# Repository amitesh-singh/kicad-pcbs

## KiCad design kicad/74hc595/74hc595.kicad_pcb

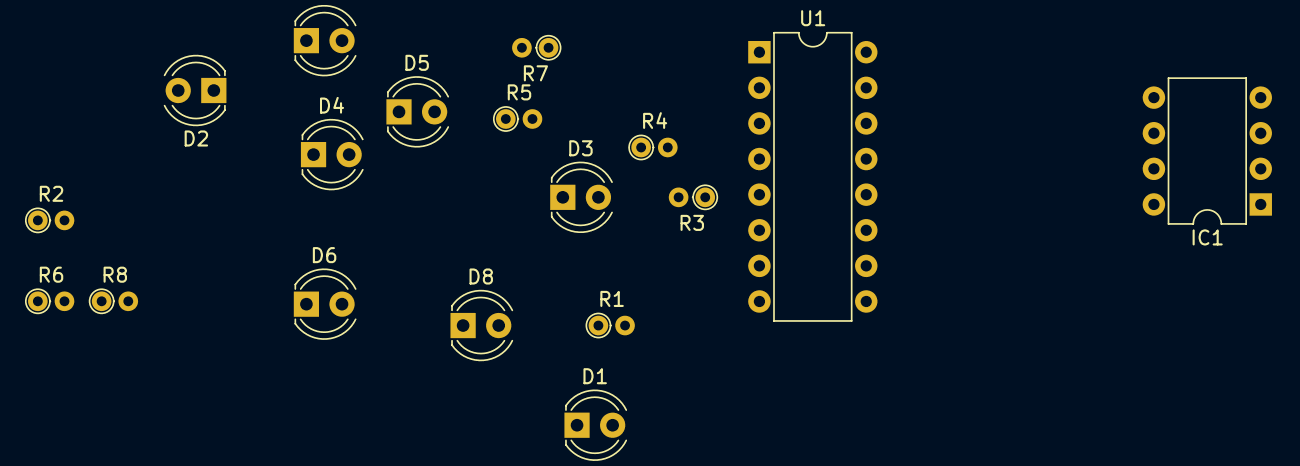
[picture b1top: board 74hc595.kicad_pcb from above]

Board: 2 copper layers, 18 parts (0 on the bottom side), 21 nets, no tracks yet.

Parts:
D1, D2, D3, D4, D5, D6, D7, D8: LED; LED_D4.0mm
IC1: ATTINY85-P; DIP-8_W7.62mm
R1, R2, R3, R4, R5, R6, R7, R8: 1k; R_Axial_DIN0204_L3.6mm_D1.6mm_P1.90mm_Vertical
U1: 74HC595; DIP-16_W7.62mm

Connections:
+5V: IC1.8, U1.10
GND: D1.1, D2.1, D3.1, D4.1, D5.1, D6.1, D7.1, D8.1, IC1.4, U1.8, U1.13
unnamed: D1.2, R1.2
unnamed: D2.2, R2.2
unnamed: D3.2, R3.2
unnamed: D4.2, R4.2
unnamed: D5.2, R5.2
unnamed: D6.2, R6.2
unnamed: D7.2, R7.2
unnamed: D8.2, R8.2
unnamed: IC1.3, U1.12
unnamed: IC1.6, U1.14
unnamed: IC1.7, U1.11
unnamed: R1.1, U1.7
unnamed: R2.1, U1.6
unnamed: R3.1, U1.5
unnamed: R4.1, U1.4
unnamed: R5.1, U1.3
unnamed: R6.1, U1.2
unnamed: R7.1, U1.1
unnamed: R8.1, U1.15

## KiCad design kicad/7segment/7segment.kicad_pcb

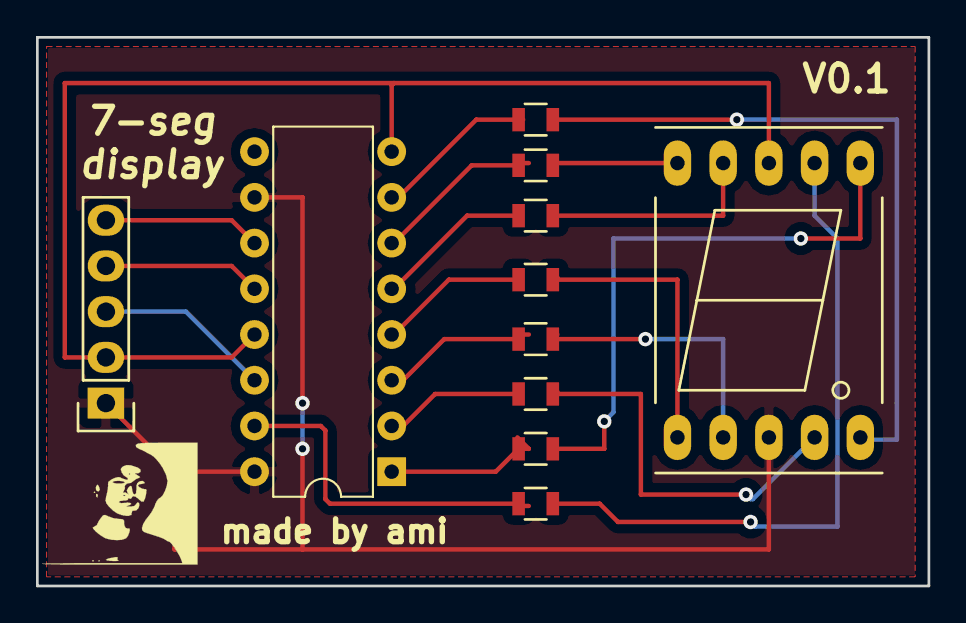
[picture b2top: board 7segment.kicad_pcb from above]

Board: 2 copper layers, 49.5 x 30.5 mm, 11 parts (0 on the bottom side), 21 nets.

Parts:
P1: CONN_01X05; Socket_Strip_Straight_1x05
R1, R2, R3, R4, R5, R6, R7, R8: 220; R_0805
S1: 7SEGM; 7SegmentLED_LTS6760_LTS6780
U1: 74HC595; DIP-16_W7.62mm

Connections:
/CLOCK: P1.4, U1.12
/DATA: P1.5, U1.11
/LATCH: P1.3, U1.14
/seg0: R8.1, U1.15
/seg1: R7.1, U1.1
/seg2: R6.1, U1.2
/seg3: R5.1, U1.3
/seg4: R4.1, U1.4
/seg5: R3.1, U1.5
/seg6: R2.1, U1.6
/seg7: R1.1, U1.7
GND: P1.2, S1.8, U1.8, U1.13
unnamed: R1.2, S1.5
unnamed: R2.2, S1.10
unnamed: R3.2, S1.9
unnamed: R4.2, S1.1
unnamed: R5.2, S1.2
unnamed: R6.2, S1.4
unnamed: R7.2, S1.6
unnamed: R8.2, S1.7
VCC: P1.1, S1.3, U1.10, U1.16

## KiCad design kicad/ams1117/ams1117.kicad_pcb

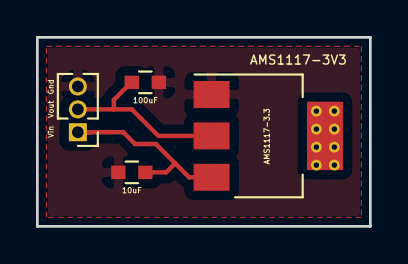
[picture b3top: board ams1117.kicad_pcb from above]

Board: 2 copper layers, 18.5 x 10.5 mm, 4 parts (0 on the bottom side), 3 nets.

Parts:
AMS1117-3.3: AMS1117-3V3; SOT-223
C1: C; C_0603
C2: 100uF; C_0603
J1: Conn_01x03; Pin_Header_Straight_1x03_Pitch1.27mm

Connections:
+5V: AMS1117-3.3.3, C1.1, J1.1
/VOUT: AMS1117-3.3.2, C2.1, J1.2
GND: AMS1117-3.3.1, C1.2, C2.2, J1.3

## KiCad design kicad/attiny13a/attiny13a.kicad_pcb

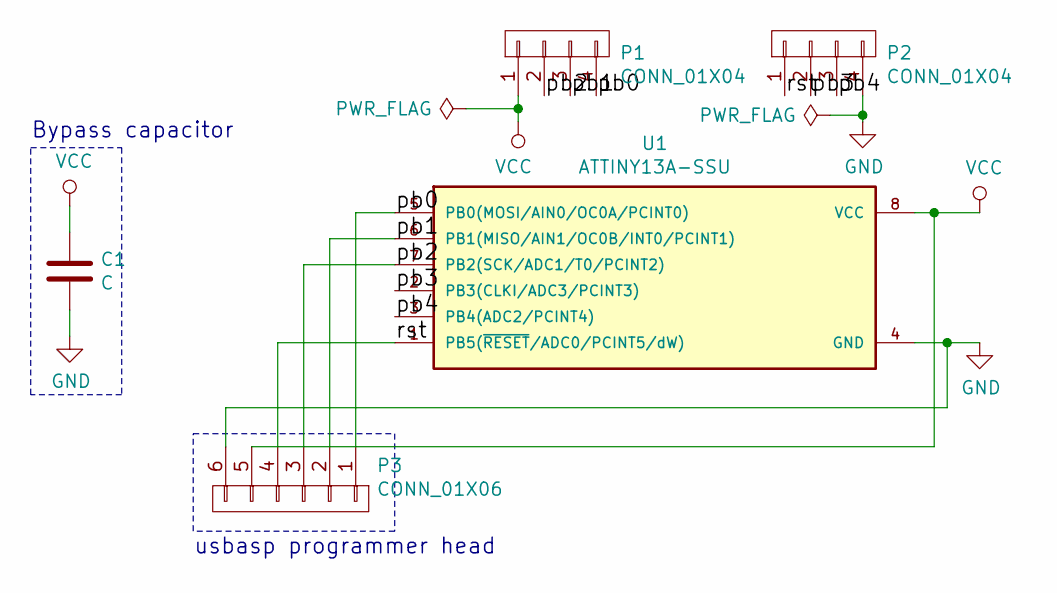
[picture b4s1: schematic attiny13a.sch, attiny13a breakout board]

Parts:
C1: C
P1, P2: CONN_01X04
P3: CONN_01X06
U1: ATTINY13A-SSU; SO8

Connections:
/pb0: P1.4, P3.1, U1.5 (PB0(MOSI/AIN0/OC0A/PCINT0))
/pb1: P1.3, P3.2, U1.6 (PB1(MISO/AIN1/OC0B/INT0/PCINT1))
/pb2: P1.2, P3.3, U1.7 (PB2(SCK/ADC1/T0/PCINT2))
/pb3: P2.2, U1.2 (PB3(CLKI/ADC3/PCINT3))
/pb4: P2.3, U1.3 (PB4(ADC2/PCINT4))
/rst: P2.1, P3.4, U1.1 (PB5(~RESET~/ADC0/PCINT5/dW))
GND: C1.2, P2.4, P3.6, U1.4 (GND)
VCC: C1.1, P1.1, P3.5, U1.8 (VCC)

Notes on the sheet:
Bypass capacitor
usbasp programmer head

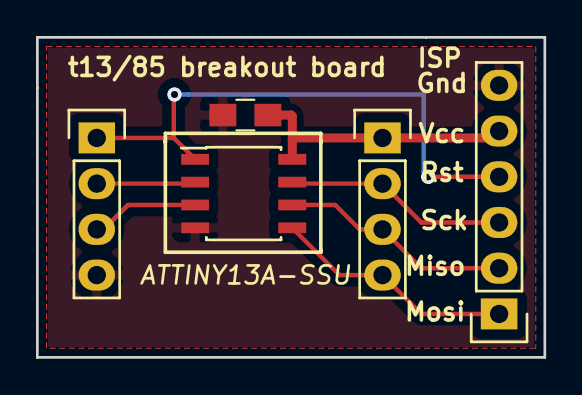
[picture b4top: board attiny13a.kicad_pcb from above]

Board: 2 copper layers, 28.2 x 17.8 mm, 5 parts (0 on the bottom side), 8 nets.

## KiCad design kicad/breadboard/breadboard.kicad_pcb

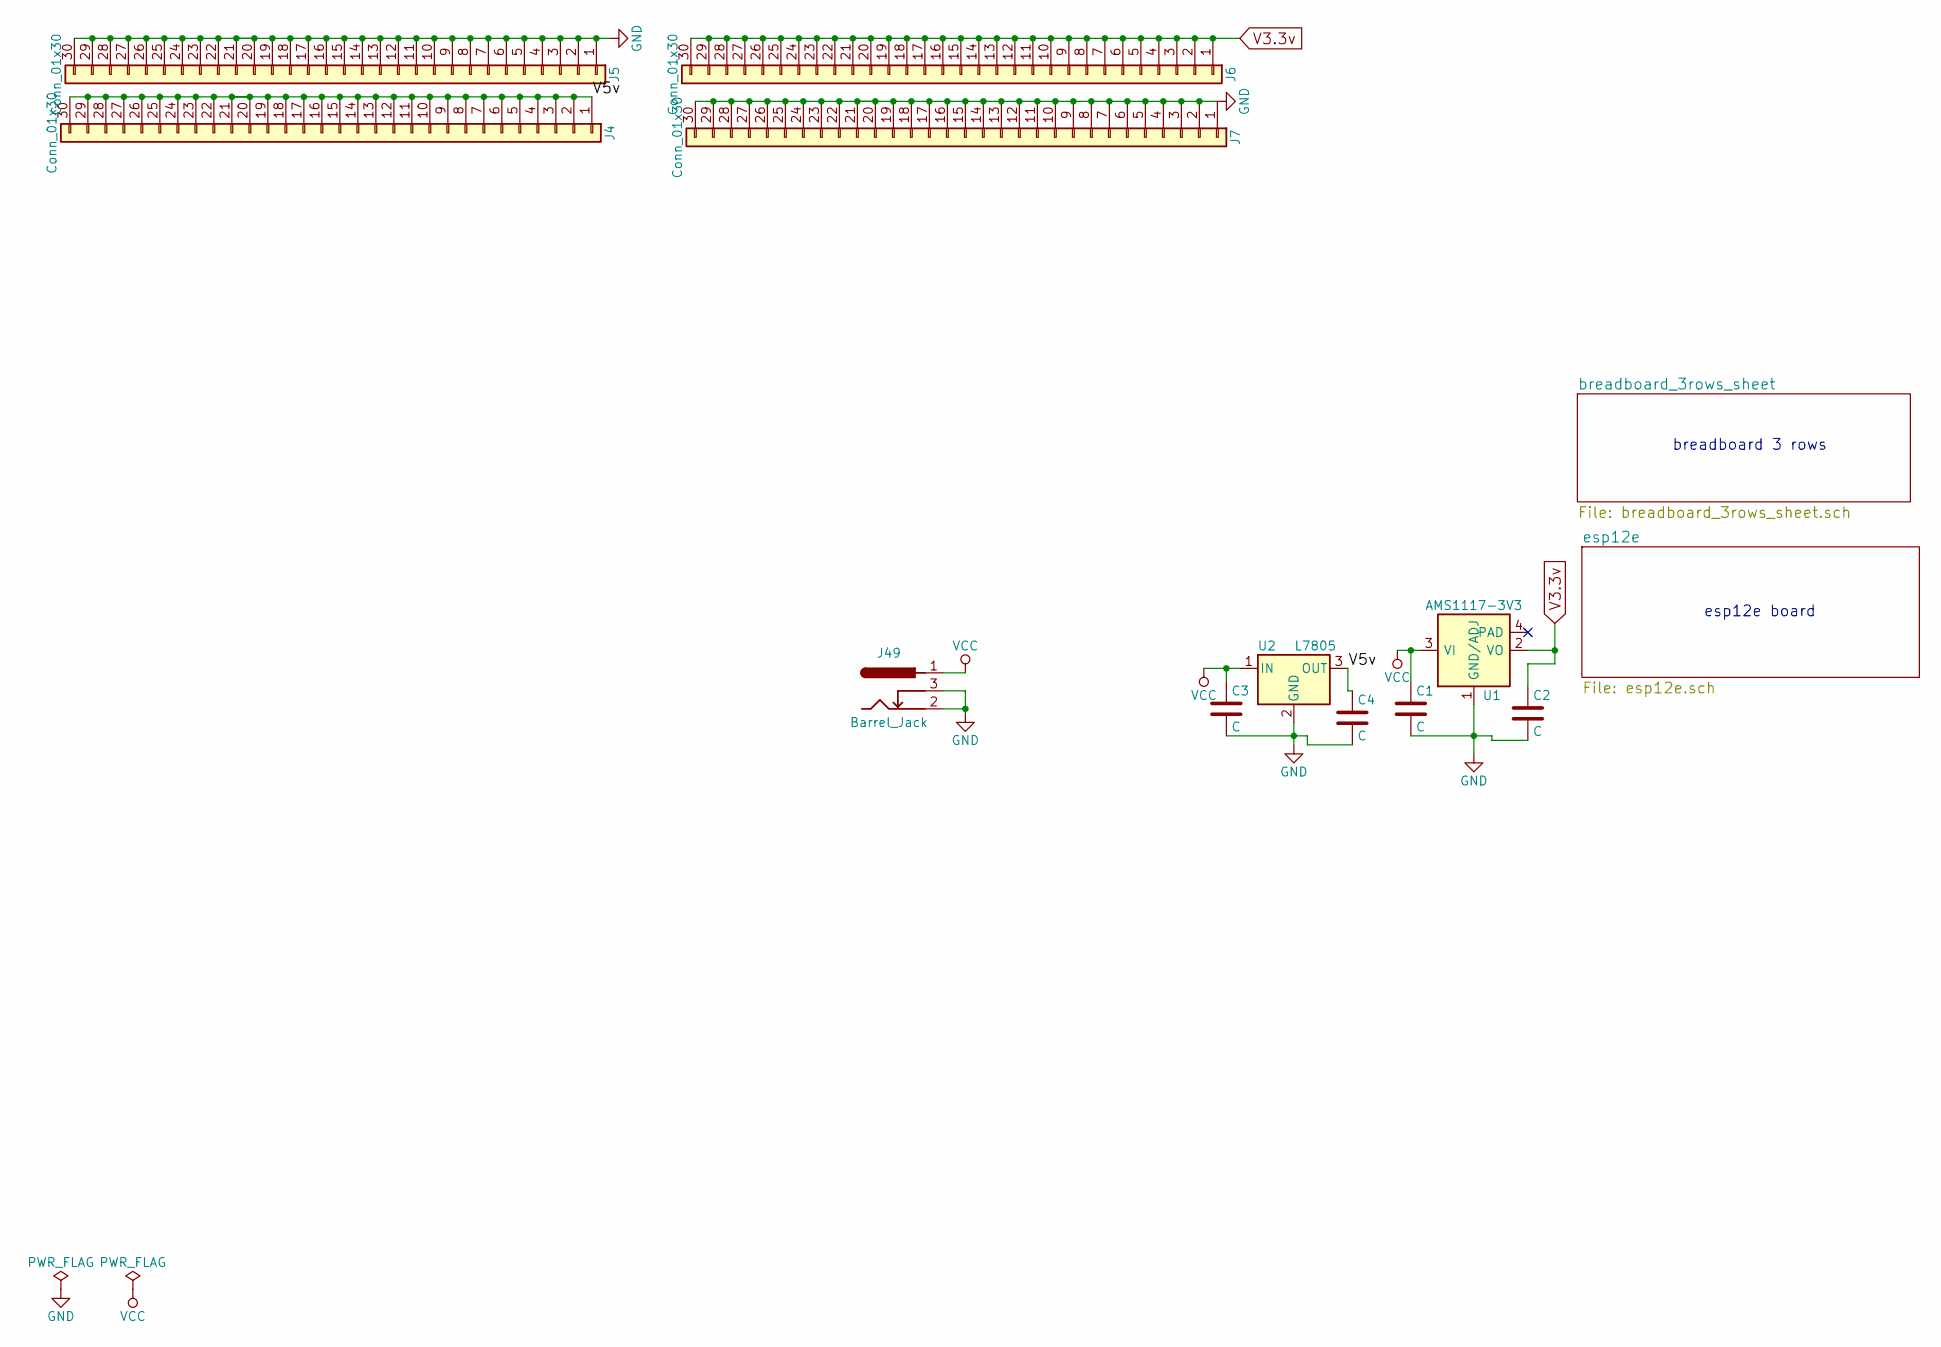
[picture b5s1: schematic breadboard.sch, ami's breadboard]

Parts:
C1, C2, C3, C4: C; C_0603_HandSoldering
J4, J5, J6, J7: Conn_01x30; Pin_Header_Straight_1x30_Pitch2.54mm
J49: Barrel_Jack; BARREL_JACK
U1: AMS1117-3V3; SOT-223; MPN LM1117
U2: L7805; TO-220

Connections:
/V5v: C4.1, J4.1, J4.2, J4.3, J4.4, J4.5, J4.6, J4.7, J4.8, J4.9, J4.10, J4.11, J4.12, J4.13, J4.14, J4.15, J4.16, J4.17, J4.18, J4.19, J4.20, J4.21, J4.22, J4.23, J4.24, J4.25, J4.26, J4.27, J4.28, J4.29, J4.30, U2.3 (OUT)
GND: C1.2, C2.2, C3.2, C4.2, J5.1, J5.2, J5.3, J5.4, J5.5, J5.6, J5.7, J5.8, J5.9, J5.10, J5.11, J5.12, J5.13, J5.14, J5.15, J5.16, J5.17, J5.18, J5.19, J5.20, J5.21, J5.22, J5.23, J5.24, J5.25, J5.26, J5.27, J5.28, J5.29, J5.30, J7.1, J7.2, J7.3, J7.4, J7.5, J7.6, J7.7, J7.8, J7.9, J7.10, J7.11, J7.12, J7.13, J7.14, J7.15, J7.16, J7.17, J7.18, J7.19, J7.20, J7.21, J7.22, J7.23, J7.24, J7.25, J7.26, J7.27, J7.28, J7.29, J7.30, J49.2, J49.3, U1.1 (GND/ADJ), U2.2 (GND); also elsewhere on the board
V3.3v: C2.1, J6.1, J6.2, J6.3, J6.4, J6.5, J6.6, J6.7, J6.8, J6.9, J6.10, J6.11, J6.12, J6.13, J6.14, J6.15, J6.16, J6.17, J6.18, J6.19, J6.20, J6.21, J6.22, J6.23, J6.24, J6.25, J6.26, J6.27, J6.28, J6.29, J6.30, U1.2 (VO); also elsewhere on the board
VCC: C1.1, C3.1, J49.1, U1.3 (VI), U2.1 (IN)

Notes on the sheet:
breadboard 3 rows
esp12e board

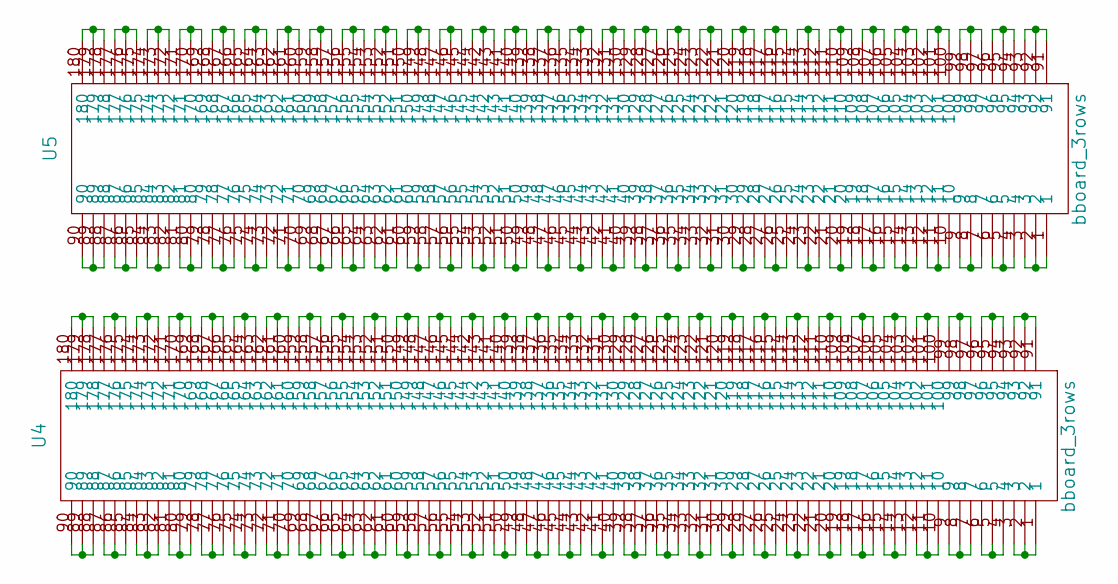
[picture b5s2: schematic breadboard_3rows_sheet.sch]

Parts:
U4, U5: bboard_3rows; bboard_3rows_footprint

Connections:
unnamed: U4.1, U4.2, U4.3
unnamed: U4.4, U4.5, U4.6
unnamed: U4.7, U4.8, U4.9
unnamed: U4.10, U4.11, U4.12
unnamed: U4.13, U4.14, U4.15
unnamed: U4.16, U4.17, U4.18
unnamed: U4.19, U4.20, U4.21
unnamed: U4.22, U4.23, U4.24
unnamed: U4.25, U4.26, U4.27
unnamed: U4.28, U4.29, U4.30
unnamed: U4.31, U4.32, U4.33
unnamed: U4.34, U4.35, U4.36
unnamed: U4.37, U4.38, U4.39
unnamed: U4.40, U4.41, U4.42
unnamed: U4.43, U4.44, U4.45
unnamed: U4.46, U4.47, U4.48
unnamed: U4.49, U4.50, U4.51
unnamed: U4.52, U4.53, U4.54
unnamed: U4.55, U4.56, U4.57
unnamed: U4.58, U4.59, U4.60
unnamed: U4.61, U4.62, U4.63
unnamed: U4.64, U4.65, U4.66
unnamed: U4.67, U4.68, U4.69
unnamed: U4.70, U4.71, U4.72
unnamed: U4.73, U4.74, U4.75
unnamed: U4.76, U4.77, U4.78
unnamed: U4.79, U4.80, U4.81
unnamed: U4.82, U4.83, U4.84
unnamed: U4.85, U4.86, U4.87
unnamed: U4.88, U4.89, U4.90
unnamed: U4.91, U4.92, U4.93
unnamed: U4.94, U4.95, U4.96
unnamed: U4.97, U4.98, U4.99
unnamed: U4.100, U4.101, U4.102
unnamed: U4.103, U4.104, U4.105
unnamed: U4.106, U4.107, U4.108
unnamed: U4.109, U4.110, U4.111
unnamed: U4.112, U4.113, U4.114
unnamed: U4.115, U4.116, U4.117
unnamed: U4.118, U4.119, U4.120
unnamed: U4.121, U4.122, U4.123
unnamed: U4.124, U4.125, U4.126
unnamed: U4.127, U4.128, U4.129
unnamed: U4.130, U4.131, U4.132
unnamed: U4.133, U4.134, U4.135
unnamed: U4.136, U4.137, U4.138
unnamed: U4.139, U4.140, U4.141
unnamed: U4.142, U4.143, U4.144
unnamed: U4.145, U4.146, U4.147
unnamed: U4.148, U4.149, U4.150
unnamed: U4.151, U4.152, U4.153
unnamed: U4.154, U4.155, U4.156
unnamed: U4.157, U4.158, U4.159
unnamed: U4.160, U4.161, U4.162
unnamed: U4.163, U4.164, U4.165
unnamed: U4.166, U4.167, U4.168
unnamed: U4.169, U4.170, U4.171
unnamed: U4.172, U4.173, U4.174
unnamed: U4.175, U4.176, U4.177
unnamed: U4.178, U4.179, U4.180
unnamed: U5.1, U5.2, U5.3
unnamed: U5.4, U5.5, U5.6
unnamed: U5.7, U5.8, U5.9
unnamed: U5.10, U5.11, U5.12
unnamed: U5.13, U5.14, U5.15
unnamed: U5.16, U5.17, U5.18
unnamed: U5.19, U5.20, U5.21
unnamed: U5.22, U5.23, U5.24
unnamed: U5.25, U5.26, U5.27
unnamed: U5.28, U5.29, U5.30
unnamed: U5.31, U5.32, U5.33
unnamed: U5.34, U5.35, U5.36
unnamed: U5.37, U5.38, U5.39
unnamed: U5.40, U5.41, U5.42
unnamed: U5.43, U5.44, U5.45
unnamed: U5.46, U5.47, U5.48
unnamed: U5.49, U5.50, U5.51
unnamed: U5.52, U5.53, U5.54
unnamed: U5.55, U5.56, U5.57
unnamed: U5.58, U5.59, U5.60
unnamed: U5.61, U5.62, U5.63
unnamed: U5.64, U5.65, U5.66
unnamed: U5.67, U5.68, U5.69
unnamed: U5.70, U5.71, U5.72
unnamed: U5.73, U5.74, U5.75
unnamed: U5.76, U5.77, U5.78
unnamed: U5.79, U5.80, U5.81
unnamed: U5.82, U5.83, U5.84
unnamed: U5.85, U5.86, U5.87
unnamed: U5.88, U5.89, U5.90
unnamed: U5.91, U5.92, U5.93
unnamed: U5.94, U5.95, U5.96
unnamed: U5.97, U5.98, U5.99
unnamed: U5.100, U5.101, U5.102
unnamed: U5.103, U5.104, U5.105
unnamed: U5.106, U5.107, U5.108
unnamed: U5.109, U5.110, U5.111
unnamed: U5.112, U5.113, U5.114
unnamed: U5.115, U5.116, U5.117
unnamed: U5.118, U5.119, U5.120
unnamed: U5.121, U5.122, U5.123
unnamed: U5.124, U5.125, U5.126
unnamed: U5.127, U5.128, U5.129
unnamed: U5.130, U5.131, U5.132
unnamed: U5.133, U5.134, U5.135
unnamed: U5.136, U5.137, U5.138
unnamed: U5.139, U5.140, U5.141
unnamed: U5.142, U5.143, U5.144
unnamed: U5.145, U5.146, U5.147
unnamed: U5.148, U5.149, U5.150
unnamed: U5.151, U5.152, U5.153
unnamed: U5.154, U5.155, U5.156
unnamed: U5.157, U5.158, U5.159
unnamed: U5.160, U5.161, U5.162
unnamed: U5.163, U5.164, U5.165
unnamed: U5.166, U5.167, U5.168
unnamed: U5.169, U5.170, U5.171
unnamed: U5.172, U5.173, U5.174
unnamed: U5.175, U5.176, U5.177
unnamed: U5.178, U5.179, U5.180

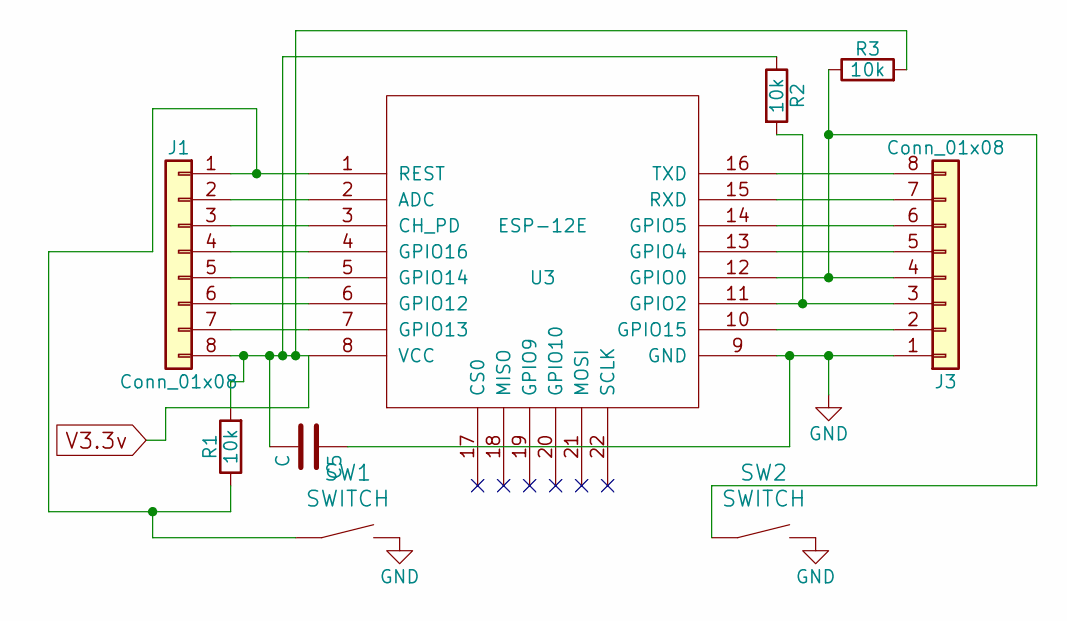
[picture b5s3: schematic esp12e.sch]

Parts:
C5: C; C_0603_HandSoldering
J1, J3: Conn_01x08; Pin_Header_Straight_1x08_Pitch2.54mm_SMD_Pin1Right
R1, R2, R3: 10k; R_0603_HandSoldering
SW1, SW2: SWITCH; SW_PUSH_6mm
U3: ESP-12E; ESP-12E_SMD

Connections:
GND: C5.1, J3.1, SW1.2, SW2.2, U3.9 (GND); also elsewhere on the board
unnamed: J1.1, R1.1, SW1.1, U3.1 (REST)
unnamed: J1.2, U3.2 (ADC)
unnamed: J1.3, U3.3 (CH_PD)
unnamed: J1.4, U3.4 (GPIO16)
unnamed: J1.5, U3.5 (GPIO14)
unnamed: J1.6, U3.6 (GPIO12)
unnamed: J1.7, U3.7 (GPIO13)
unnamed: J3.2, U3.10 (GPIO15)
unnamed: J3.3, R2.2, U3.11 (GPIO2)
unnamed: J3.4, R3.1, SW2.1, U3.12 (GPIO0)
unnamed: J3.5, U3.13 (GPIO4)
unnamed: J3.6, U3.14 (GPIO5)
unnamed: J3.7, U3.15 (RXD)
unnamed: J3.8, U3.16 (TXD)
V3.3v: C5.2, J1.8, R1.2, R2.1, R3.2, U3.8 (VCC); also elsewhere on the board

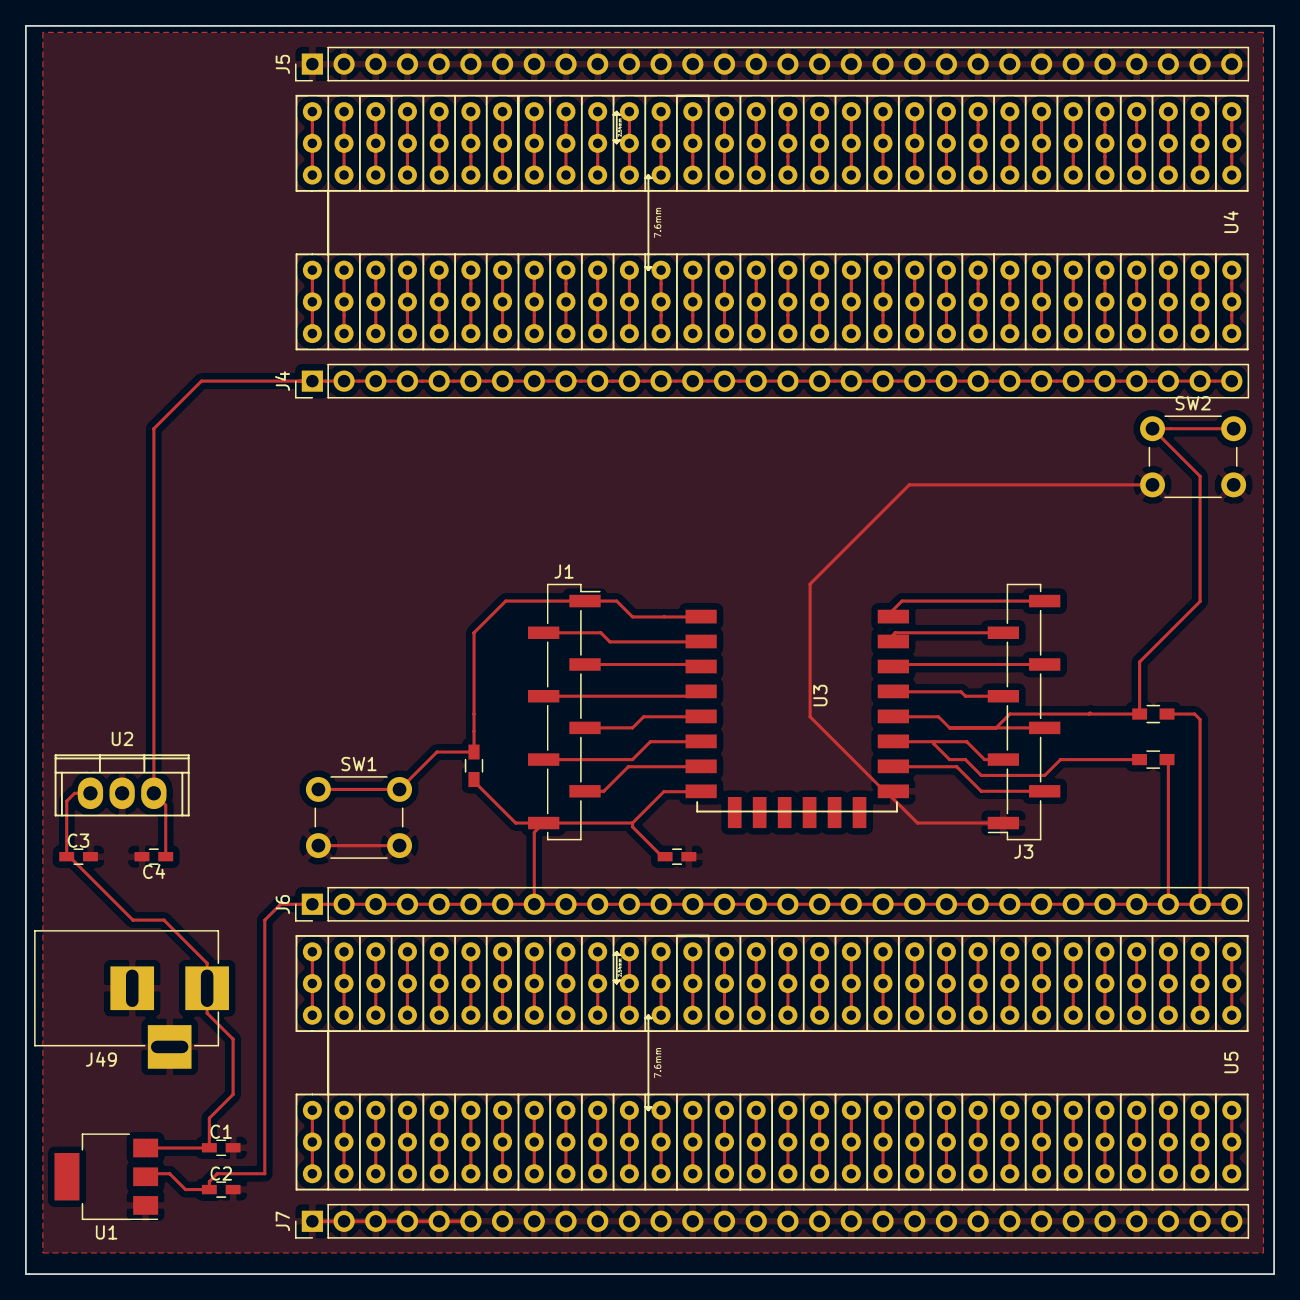
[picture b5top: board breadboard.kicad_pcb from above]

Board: 2 copper layers, 100.0 x 100.0 mm, 22 parts (0 on the bottom side), 138 nets.

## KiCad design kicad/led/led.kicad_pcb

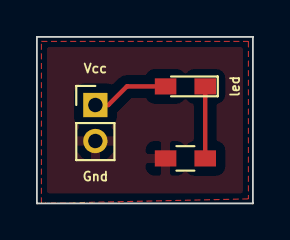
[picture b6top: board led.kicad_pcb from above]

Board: 2 copper layers, 12.0 x 9.2 mm, 3 parts (0 on the bottom side), 3 nets.

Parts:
J1: Conn_01x02; Pin_Header_Straight_1x02_Pitch2.00mm
R1: R; R_0603_HandSoldering
led: LED; LED_0603_HandSoldering

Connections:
GND: J1.2, R1.2
unnamed: R1.1, led.1
VCC: J1.1, led.2
